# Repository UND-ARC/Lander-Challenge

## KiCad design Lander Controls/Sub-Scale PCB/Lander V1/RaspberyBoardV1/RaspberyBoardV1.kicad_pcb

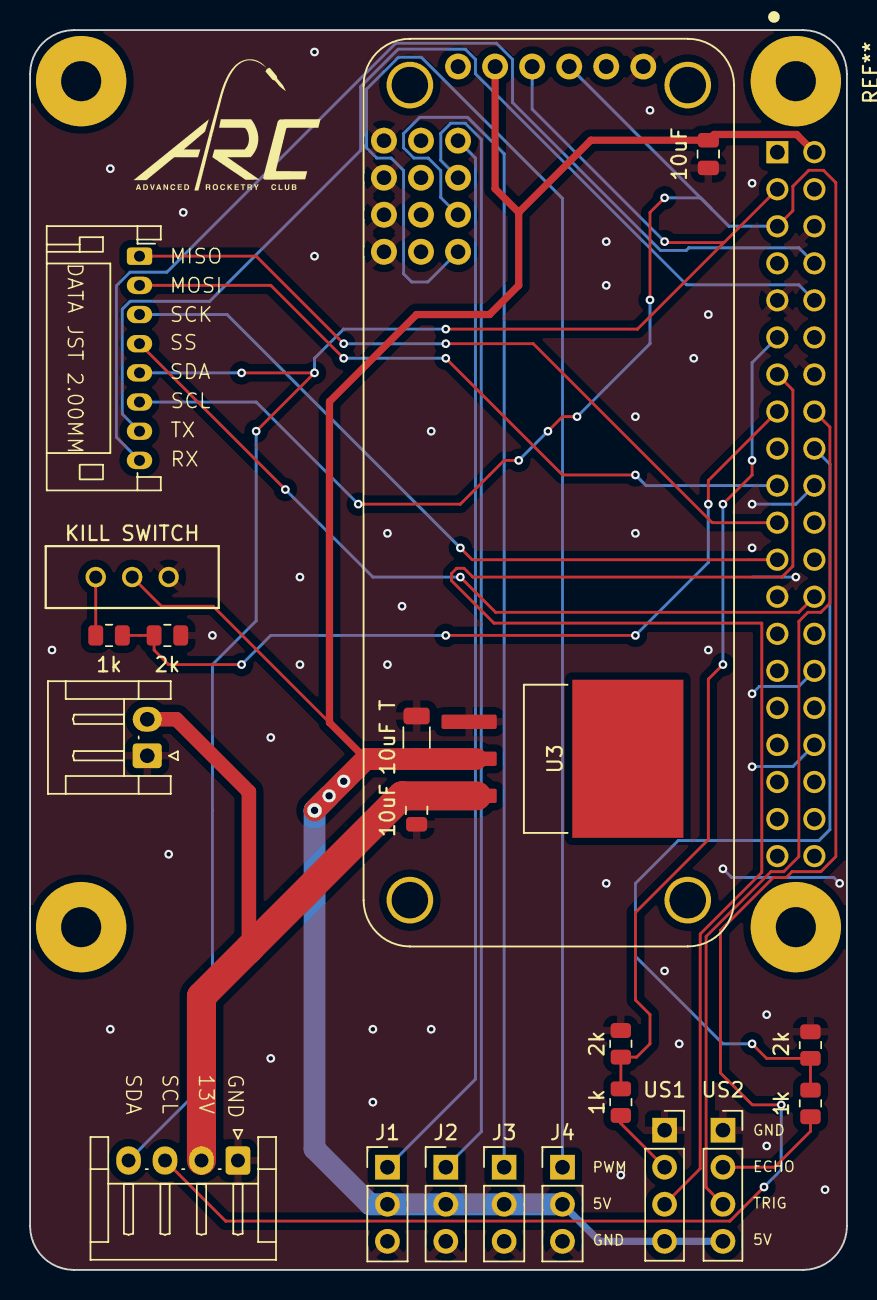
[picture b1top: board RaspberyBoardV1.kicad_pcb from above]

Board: 2 copper layers, 56.0 x 85.0 mm, 18 parts (0 on the bottom side), 14 nets.

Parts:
1k, 1k#2, 1k#3, 2k, 2k#2, 2k#3: R_0805_2012Metric
10uF, 10uF#2: C_0805_2012Metric
10uF T: C_1206_3216Metric
J1, J2, J3, J4: PinHeader_1x03_P2.54mm_Vertical
KILL SWITCH: SW_1218_EWI
U1: 815; MODULE_815
U3: TO254P1524X483-4N
US1, US2: PinSocket_1x04_P2.54mm_Vertical

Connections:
5V2: 10uF.1, 10uF T.2, J1.2, J2.2, J3.2, J4.2, KILL SWITCH.2, U1.VCC_1 (VCC), U3.2, US1.4, US2.4
ECHO1: 1k#3.1, US1.2
ECHO1.3v: 1k#3.2, 2k#2.1
ECHO2: 1k.1, US2.2
ECHO2.3v: 1k.2, 2k.1
GND: 2k.2, 2k#2.2, 2k#3.2, 10uF.2, 10uF T.1, 10uF#2.2, J1.3, J2.3, J3.3, J4.3, KILL SWITCH.3, U1.GND_1 (GND), U1.GND_3 (GND), U1.GND_4 (GND), U1.GND_5 (GND), U1.GND_6 (GND), U3.1, US1.1, US2.1
KILLSWITCH: 1k#2.2, 2k#3.1
KS5V: 1k#2.1, KILL SWITCH.1
PWM1: J1.1, U1.0 (PWM_0)
PWM2: J2.1, U1.1 (PWM_1)
PWM3: J3.1, U1.2 (PWM_2)
PWM4: J4.1, U1.3 (PWM_3)
V+: U1.V+_1 (V+), U1.V+_3 (V+), U1.V+_4 (V+), U1.V+_5 (V+), U1.V+_6 (V+)
VCC1: 10uF#2.1, U3.3

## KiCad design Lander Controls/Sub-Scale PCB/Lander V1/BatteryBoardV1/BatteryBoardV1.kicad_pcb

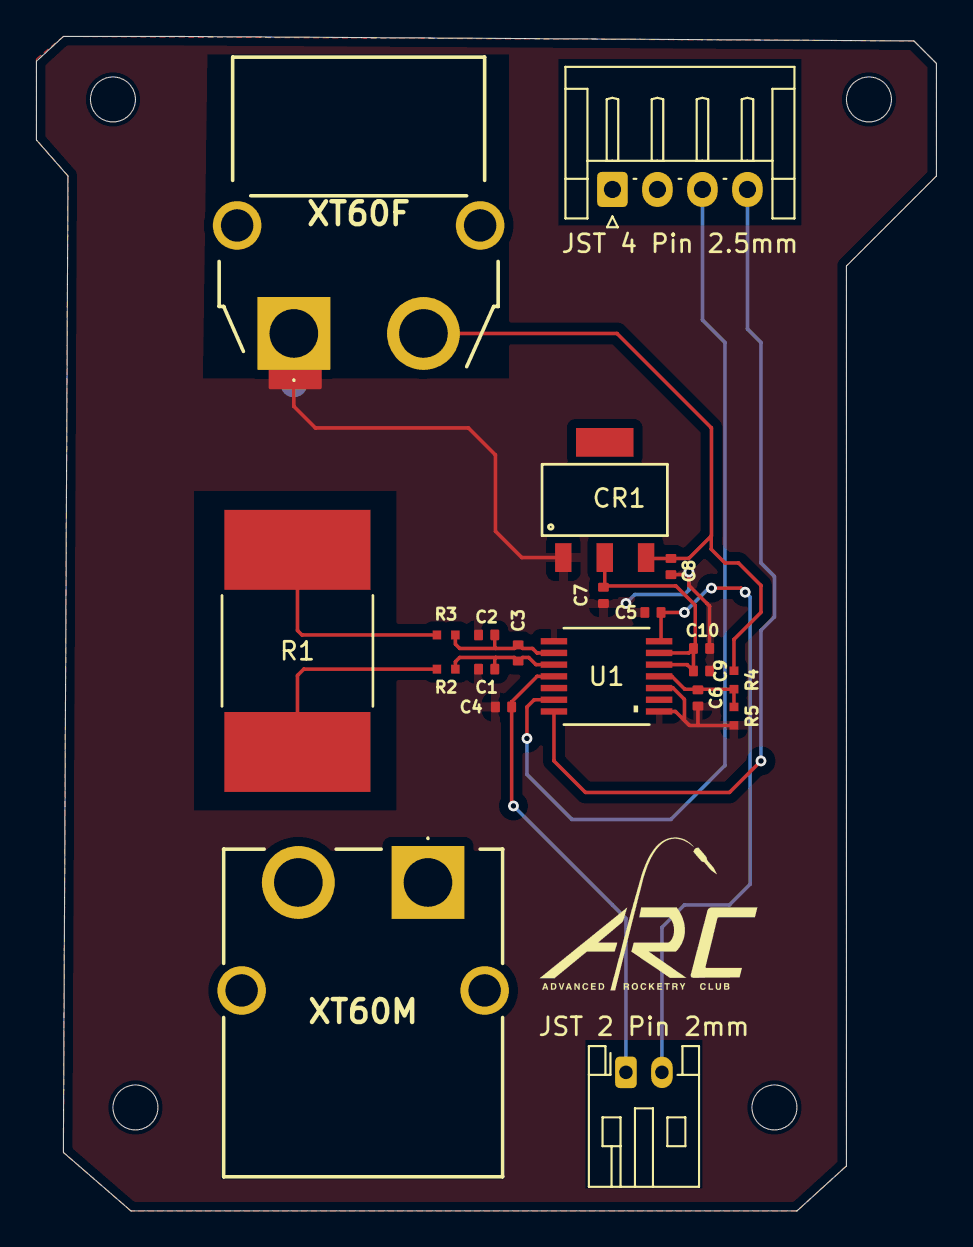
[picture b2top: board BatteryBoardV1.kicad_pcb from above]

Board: 2 copper layers, 50.0 x 65.2 mm, 22 parts (0 on the bottom side), 11 nets.

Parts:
C1, C2, C3, C4, C5, C6, C7, C8, C9, C10: CAPC1005X55N
CR1: SOT-223_STM
JST 2 Pin 2mm: JST_PH_S2B-PH-K_1x02_P2.00mm_Horizontal
JST 4 Pin 2.5mm: JST_EH_S4B-EH_1x04_P2.50mm_Horizontal
LOGO: LOGO
R1: RES_WSLP5931_.002OHM_VIS
R2, R3, R4, R5: RES_ERA2AEB101X
U1: PW14_TEX
XT60F: XT60PWF
XT60M: XT60PWM

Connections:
2.5v: C5.1, JST 2 Pin 2mm.2, U1.7
3.3v: C7.2, C9.2, C10.2, CR1.2, U1.5, U1.6
BAT+: C8.1, CR1.3, R4.2, XT60F.2
BATD: C6.2, R4.1, R5.2, U1.4
GND: C1.2, C2.1, C4.1, C5.2, C6.1, C7.1, C8.2, C9.1, C10.1, CR1.1, R5.1, U1.1, U1.3, U1.8, XT60F.1
NC: U1.2, U1.12, XT60M.1, XT60M.2
SCL: JST 4 Pin 2.5mm.3, U1.13
SDA: JST 4 Pin 2.5mm.4, U1.14
SRN: C1.1, C3.2, R1.2, R2.1, R2.2, U1.10
SRP: C2.2, C3.1, R1.1, R3.1, R3.2, U1.9
TR-: C4.2, JST 2 Pin 2mm.1, U1.11

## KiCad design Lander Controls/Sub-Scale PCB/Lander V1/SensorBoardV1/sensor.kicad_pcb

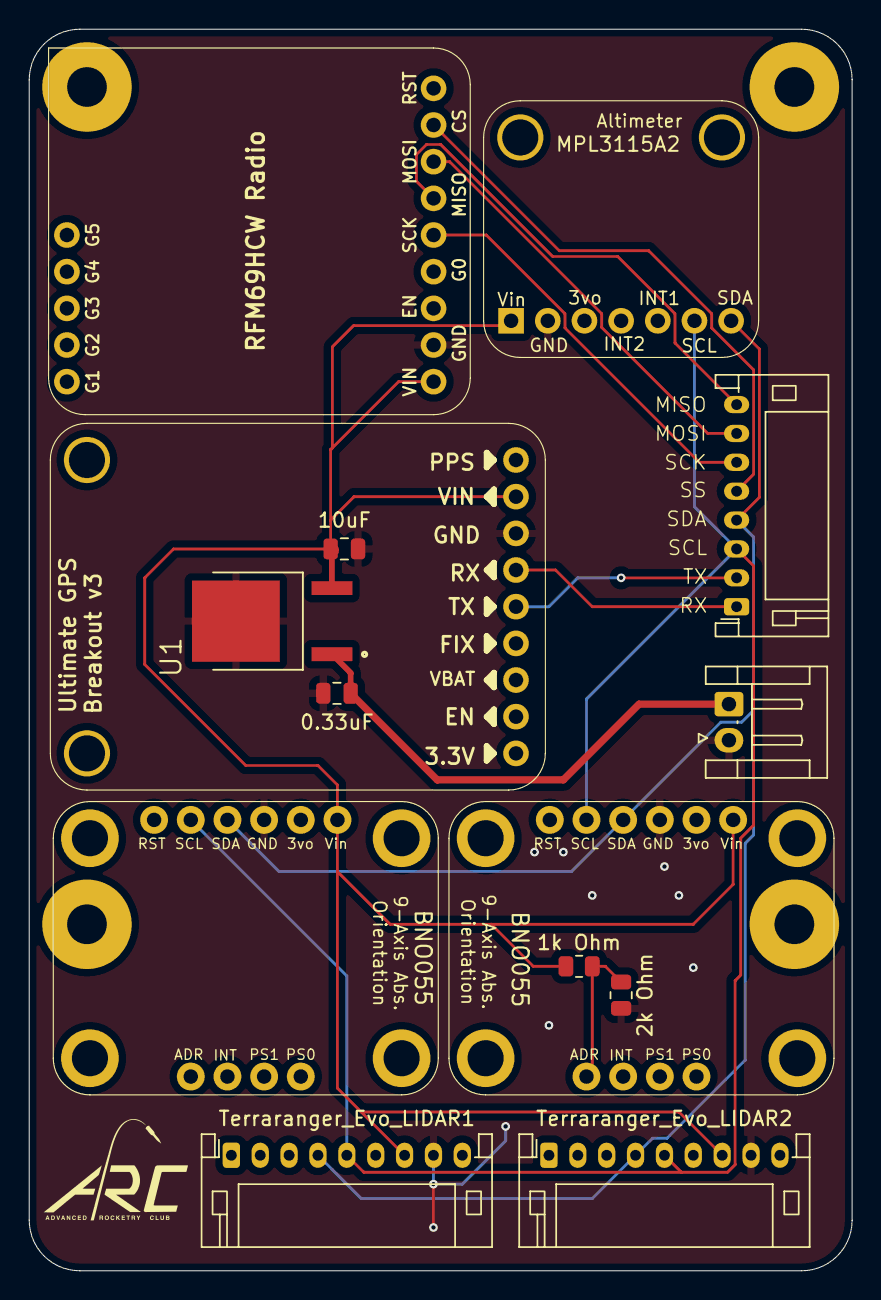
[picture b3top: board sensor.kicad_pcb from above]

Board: 2 copper layers, 57.0 x 86.0 mm, 13 parts (1 on the bottom side), 6 nets.

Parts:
0.33uF, 10uF: C2; C_0805_2012Metric
1k Ohm, 2k Ohm: R_0805_2012Metric
BNO55, BNO0551: BNO055
MPL3115A2Barometer1: MPL3115A2
PA1616SGPS1: PA1616S
RFM95WLoRaRadio1: RFM69
Terraranger_Evo_LIDAR1, Terraranger_Evo_LIDAR2: JST_PH_S9B-PH-K_1x09_P2.00mm_Horizontal
U1: MC7805BDTRKG; DPAK229P990X238-4N
U2: RASPBERRY_PI_4B_4GB; MODULE_RASPBERRY_PI_4B_4GB

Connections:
/3V: 1k Ohm.2, 2k Ohm.1, BNO55.4 (ADR)
/5V: 1k Ohm.1, 10uF.2, BNO55.5 (VIN), BNO0551.5 (VIN), MPL3115A2Barometer1.1 (Vin), PA1616SGPS1.8 (VIN), RFM95WLoRaRadio1.1 (VIN), Terraranger_Evo_LIDAR1.7 (5V), Terraranger_Evo_LIDAR2.7 (5V), U1.3 (OUT)
/GND: 0.33uF.1, 2k Ohm.2, 10uF.1, BNO55.7 (GND), BNO0551.7 (GND), MPL3115A2Barometer1.2 (GND), PA1616SGPS1.7 (GND), RFM95WLoRaRadio1.2 (GND), Terraranger_Evo_LIDAR1.8 (GND), Terraranger_Evo_LIDAR2.8 (GND), U1.2 (GND)
/SCL: BNO55.9 (SCL), BNO0551.9 (SCL), MPL3115A2Barometer1.6 (SCL), Terraranger_Evo_LIDAR1.5 (SCL), Terraranger_Evo_LIDAR2.5 (SCL)
/SDA: BNO55.8 (SDA), BNO0551.8 (SDA), MPL3115A2Barometer1.7 (SDA), Terraranger_Evo_LIDAR1.4 (SDA), Terraranger_Evo_LIDAR2.4 (SDA)
VCC: 0.33uF.2, U1.1 (IN)

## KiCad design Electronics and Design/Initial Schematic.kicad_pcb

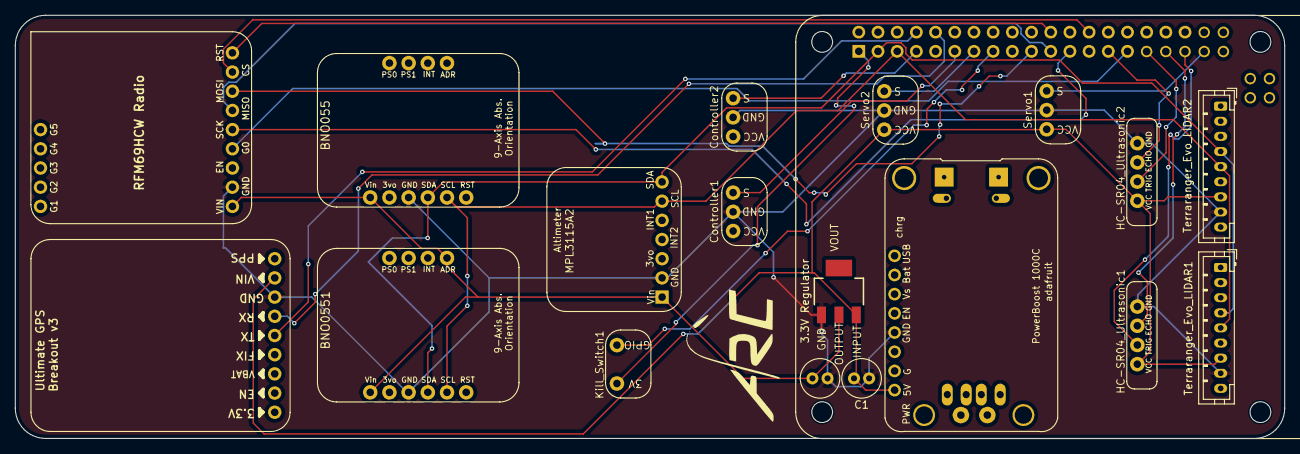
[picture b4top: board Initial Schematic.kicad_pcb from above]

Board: 2 copper layers, 168.0 x 56.0 mm, 19 parts (0 on the bottom side), 25 nets.

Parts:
3.3V Regulator: 3.3V_Voltage_Regulator
Adafruit_Powerboost1: Adafruit Powerboost
BNO55, BNO0551: BNO055
C1, C2: C; C_Radial_D5.0mm_H11.0mm_P2.00mm
Controller1, Controller2: Controller
HC-SR04_Ultrasonic1, HC-SR04_Ultrasonic2: HC-SR04 Ultrasonic
J1: Raspberry_Pi_2_3; raspberrypi_2_3
Kill_Switch1: Kill Switch
MPL3115A2Barometer1: MPL3115A2
PA1616SGPS1: PA1616S
RFM95WLoRaRadio1: RFM69
Servo1, Servo2: Servo
Terraranger_Evo_LIDAR1, Terraranger_Evo_LIDAR2: JST_PH_B9B-PH-K_1x09_P2.00mm_Vertical

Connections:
/3V: 3.3V Regulator.2 (OUTPUT), BNO55.5 (VIN), BNO0551.4 (ADR), BNO0551.5 (VIN), C2.1, MPL3115A2Barometer1.1 (Vin), RFM95WLoRaRadio1.1 (VIN)
/3V3: J1.1 (3V3), J1.17 (3V3), Kill_Switch1.1 (3V)
/5V: 3.3V Regulator.3 (INPUT), Adafruit_Powerboost1.8 (5V), C1.1, HC-SR04_Ultrasonic1.1 (VCC), HC-SR04_Ultrasonic2.1 (VCC), PA1616SGPS1.8 (VIN), Servo1.1 (VCC), Servo2.1 (VCC), Terraranger_Evo_LIDAR1.7 (5V), Terraranger_Evo_LIDAR2.7 (5V)
/CS: J1.26 (~CE1/GPIO7), RFM95WLoRaRadio1.8 (CS)
/ECHO1: HC-SR04_Ultrasonic1.3 (ECHO), J1.33 (PWM1/GPIO13)
/ECHO2: HC-SR04_Ultrasonic2.3 (ECHO), J1.27 (ID_SD/GPIO0)
/GND: 3.3V Regulator.1 (GND), Adafruit_Powerboost1.5 (GND), BNO55.7 (GND), BNO0551.7 (GND), C1.2, C2.2, Controller1.4 (GND), Controller2.4 (GND), HC-SR04_Ultrasonic1.4 (GND), HC-SR04_Ultrasonic2.4 (GND), MPL3115A2Barometer1.2 (GND), PA1616SGPS1.7 (GND), RFM95WLoRaRadio1.2 (GND), Servo1.2 (GND), Servo2.2 (GND), Terraranger_Evo_LIDAR1.8 (GND), Terraranger_Evo_LIDAR2.8 (GND)
/GO: J1.29 (GCLK1/GPIO5), RFM95WLoRaRadio1.4 (G0)
/GPIO: J1.15 (GPIO22), Kill_Switch1.2 (GPIO)
/MISO: J1.21 (MISO0/GPIO9), RFM95WLoRaRadio1.6 (MISO)
/MOSI: J1.19 (MOSI0/GPIO10), RFM95WLoRaRadio1.7 (MOSI)
/Motor1: Controller1.5 (Signal), J1.11 (GPIO17)
/Motor2: Controller2.5 (Signal), J1.7 (GCLK0/GPIO4)
/RST1: J1.22 (GPIO25), RFM95WLoRaRadio1.9 (RST)
/RX: J1.10 (GPIO15/RXD), PA1616SGPS1.6 (RX)
/SCK: J1.23 (SCLK0/GPIO11), RFM95WLoRaRadio1.5 (SCK)
/SCL: BNO55.9 (SCL), BNO0551.9 (SCL), J1.5 (SCL/GPIO3), MPL3115A2Barometer1.6 (SCL), Terraranger_Evo_LIDAR1.5 (SCL), Terraranger_Evo_LIDAR2.5 (SCL)
/SDA: BNO55.8 (SDA), BNO0551.8 (SDA), J1.3 (SDA/GPIO2), MPL3115A2Barometer1.7 (SDA), Terraranger_Evo_LIDAR1.4 (SDA), Terraranger_Evo_LIDAR2.4 (SDA)
/Servo1: J1.37 (GPIO26), Servo1.3 (Signal)
/Servo2: J1.13 (GPIO27), Servo2.3 (Signal)
/TRIG1: HC-SR04_Ultrasonic1.2 (TRIG), J1.35 (GPIO19/MISO1)
/TRIG2: HC-SR04_Ultrasonic2.2 (TRIG), J1.31 (GCLK2/GPIO6)
/TX: J1.8 (GPIO14/TXD), PA1616SGPS1.5 (TX)
unnamed: J1.2 (5V), J1.4 (5V)
unnamed: J1.6 (GND), J1.9 (GND), J1.14 (GND), J1.20 (GND), J1.25 (GND), J1.30 (GND), J1.34 (GND), J1.39 (GND)

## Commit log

2025-02-27 Added basic motor controls test to calibrate it
2025-02-28 Updated code to include Christian's servo control
2025-02-28 Updated to make gimbal angles accurate
2025-02-28 Updated to include floats, need to invert formula for angle
2025-02-28 Experimenting with inverting the system
2025-02-28 Reverse engineered servo code using dictionaries
2025-03-02 Updated servo code to go to nearest value
2025-03-02 Added comments to make it more readable
2025-03-03 Added code for second servo and shifted angle by 90 to account for servo motion
2025-03-06 Added code for second motor controller
2025-03-06 Create Monitoring Motor Thrust
2025-03-06 Added the library for the load cell
2025-03-07 Added load cell code
2025-03-07 Updated with experimental code
2025-03-07 Updated code to test loadcell
2025-03-07 Updated load cell to also measure time
2025-03-07 Fixed small error
2025-03-07 Changed function used
2025-03-07 Updated to include new library
2025-03-07 Switched libraries, slightly more accurate at measuring weight
2025-03-09 Added bno055 imu sample code
2025-03-09 Switched to newer BNO055 library
2025-03-09 Updated with folders for increased readability
2025-03-09 Improved Code Readability
2025-03-09 Added description of the electronics and designs for future years
2025-03-09 Updated to include the test procedure we used for the gimbal
2025-03-10 Added LIDAR sample code
2025-03-10 Updated LIDAR and IMU code to function properly with our tests
2025-03-11 Updated load cell code with some calibrations, still didn't fix the issue
2025-03-11 Updated code to include calibration, still has some data spikes
2025-03-11 Added arduino load cell code, confirmed it already works
2025-03-11 Updated code to include timer and to end after 32 seconds
2025-03-11 Changed code to be readable using PUTTY for easy insertion into excel
2025-03-11 Changed the code to be used in excel, for real this time
2025-03-12 Added code to test motor using arduino, needed to test with load cell
2025-03-12 Added code for arduino motor read
2025-03-12 Updated code to use quartenions to measure the angle and convert it into degrees
2025-03-12 Made it so motor thrust increases and then decreases
2025-03-17 Updated code to go from 0-180
2025-03-21 Adde ultrasonic code for LIDAR blindspots
2025-03-24 Added LIDAR address change code
2025-03-24 Found Data for IMU and set up code for recording on IMU and LIDAR
2025-03-24 Found LIDAR data
2025-03-25 Updated LIDAR change address code
2025-03-25 Updated to include command to tell it to change address
2025-03-26 Ultrasonic Test Data
2025-03-26 Changed address to 30 for LIDAR
2025-03-26 Added way to have multiple IMU, wasn't importing correctly
2025-03-26 Added comments explaining IMU addresses
2025-03-26 New Folder For Ground Support
2025-03-27 Added LORA test code and folder
2025-03-29 Added folder for sensor test data for increased readability
2025-03-29 Added Circuit Schematic and PCB designs
2025-03-31 Made code for controlling gimbal with IMU
2025-03-31 Adjusted IMU code with gimbal mechanism
2025-04-01 Updated IMU code so y-axis is no longer locked between -90 and 90 degrees
2025-04-01 Updated IMU Code to filter unwanted movements in pitch and yaw.
2025-04-02 Added IMU calibration code
2025-04-02 Updated calibration code to place file in different path
2025-04-02 Uncommented magnetometer, even though it is unnecesary
2025-04-02 Added IMU webcode, allows us to test IMU with visual
2025-04-02 Moved Adafruit_CircuitPython_BNO055 to libraries
2025-04-02 Added IMU calibration
2025-04-02 Updated calibratiom data
2025-04-03 Added ability to change IMU mode between absolute and relative
2025-04-03 Added ability to calibrate and switched to relative orientation
2025-04-11 Made slight changes to orientation and calibration
2025-04-13 Updated gimbal with IMU so it now works, needs some tuning to fix some erroneous actions
2025-04-13 Added calibration data for second IMU
2025-04-14 Updated PID tunings using values gotten from load cell.
2025-04-14 Added Arduino Motor Thrust Monitoring Code
2025-04-14 Added motor test data
2025-04-14 Updated Arduino motor read code
2025-04-15 Removed Unnecesary Component File
2025-04-15 Updated KiCAD files to easier to understand for new users
2025-04-16 Added incremental motor test data where it was increased by intervals of 20 degrees
2025-04-16 Added arduino code to incrementally monitor motor thrust using 20 degree intervals
2025-04-25 Made code to control the motor and the gimbal at the same time. No sensors.
2025-04-25 Updated code to ensure motor works properly
2025-04-28 Adjusted tuning of PID
2025-05-02 Added updated motor thrust code
2025-05-22 Add files via upload
    Current Ignitor LABVIEW files
2025-05-22 Added LABVIEW documentation for reference
2025-05-22 Removed LABVIEW pdf from main file
2025-05-23 Added global variable file so project runs correctly
2025-11-30 Initial orrifice sizing calculator
2025-12-03 Added Outdated Files and GUI-Python folders
2025-12-03 added files to repository
2025-12-04 added more igniter calcs and 3d plot for A x Mdot x Delta P
2025-12-10 Add Prometheus config and licensing files
2026-02-19 added ignitor test python gui code
2026-02-21 added labjack connection, untested
2026-02-21 fixed minor syntax error
2026-02-22 Testing Labjack integration
2026-02-22 potential fix
2026-02-22 Tested thermocouple
2026-02-22 connected other labjack outputs and gui buttons
2026-02-22 added go no status
2026-02-22 oop forgot to import new gui
2026-02-23 Changed some stuff
2026-02-26 added a graph
2026-02-26 logging and graph work
2026-02-27 added some code for mass flow, not done yet need Derek's help
2026-02-27 started work on a second window for graphs
2026-02-28 started mass flow calculations
2026-03-04 created a python program to test LORA
2026-03-04 changed some testings stuff
2026-03-04 gps test
2026-03-04 send and recive text
2026-03-04 Servo Test Script
2026-03-04 Updated Servo Test
2026-03-04 send and recive test
2026-03-04 changed some file paths
2026-03-04 Created BN055 and Bar sensor
2026-03-04 did some things idk
2026-03-04 configed radio
2026-03-04 test if it is reciving noise
2026-03-04 more configs stuff
2026-03-05 fix error on start
2026-03-05 fixes
2026-03-05 changed logging
2026-03-05 changed logging agin
2026-03-05 changed logging again
2026-03-16 moved start logic outside of loop
2026-03-16 somthing
2026-03-16 trying to deinit the pins
2026-03-16 made the listener hand off the pins
2026-03-16 added more print statments
2026-03-16 import error lol
2026-03-16 ahhhh
2026-03-16 ahhhhhhhhhhhh
2026-03-18 some updates
2026-03-24 Updates to GUI
    GUI has been drastically overhauled since last update. Exclusively runs through Python. I havent been able to get the program to run without launching it through PyCharm. Reference readme.txt.txt for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
2026-03-25 Updated GUI
    GUI updates:
    * minor optimization
    * support for 56 channels
    * polling rate reduced to 300hz
    * added feature where if voltage is over 10 (the default if nothing is connected) there should be a small red dot next to that analog pin on the GUI
    * changed from single blanket "threshold voltage" to individual voltages on each sensor. Can only be configured in the code.
2026-03-30 make rssi print constanlty now
2026-03-30 added heartbeat
2026-03-31 changed back
2026-03-31 GNU radio is dumb
2026-03-31 plz work
2026-03-31 plz workk
2026-03-31 screams
2026-03-31 added time out
2026-03-31 ahhhhhhh
2026-03-31 plzz i want to go home
2026-03-31 cries
2026-03-31 alright last chance before i go home
2026-03-31 okay last one for sure
2026-04-08 update
    added support for all outputs
2026-04-08 Added support for presets software to include thresholds
    The presets software now allows for any threshold to be set within it. It features automatic conversions for sensors actual units, rather than just putting in voltages. Not all pins are configured ye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
2026-04-14 LQR Folder
2026-04-16 Bug fixes and general updates
    bug fixes:
    analog outputs error when not converting from % to volts fixed
    preset software not overwriting files when using “open” instead of new file fixed
    Fixed relay pinouts
    fixed error where NC and NO valves wouldn't sync properly between presets and main softwares
    fixed "stop+save+kill isn't killing" error
2026-04-17 testing
2026-04-18 added class files for subsystems
2026-04-23 minor updates
    - Fixed kill button
    - added the name of the preset file into the log file name
    - kill button now sets everything to 0 before the program ends
    - skips .bin, saves directly to .csv now.
2026-04-24 Sub-Scale Contorl Python Update 1
2026-04-25 claude rewrote the lander radio comms
2026-04-25 debuging
2026-04-25 debuging 2
2026-04-25 works
2026-04-25 Lander Control Update 4/25/26 12:00PM
2026-04-26 Lander Controls Update 4/25/26 10:00 PM
2026-05-06 Fixed AIN
    Added corrected AIN values for reading the pressure transducers and thermocouples
2026-05-07 Alpha 1.0
    Changes:
    - Minor changes
    - addition of Operators Manual 1.0
    This is the official Alpha 1.0 release. Releases will bb tracked for ease of use with the user manual.
2026-05-07 Alpha 1.0.1
    Changes:
    - changed graph range from -0.1V to 5.1V to a range of -0.1V to 10.1V
2026-05-07 Alpha 1.0.1
    Changes:
    - updated Operators Manual
2026-05-14 mostly works
2026-05-19 Fix and data
    Fixed several timing issues. Added additional safety features. Added cold flow test data.
2026-06-22 Added PCB files
